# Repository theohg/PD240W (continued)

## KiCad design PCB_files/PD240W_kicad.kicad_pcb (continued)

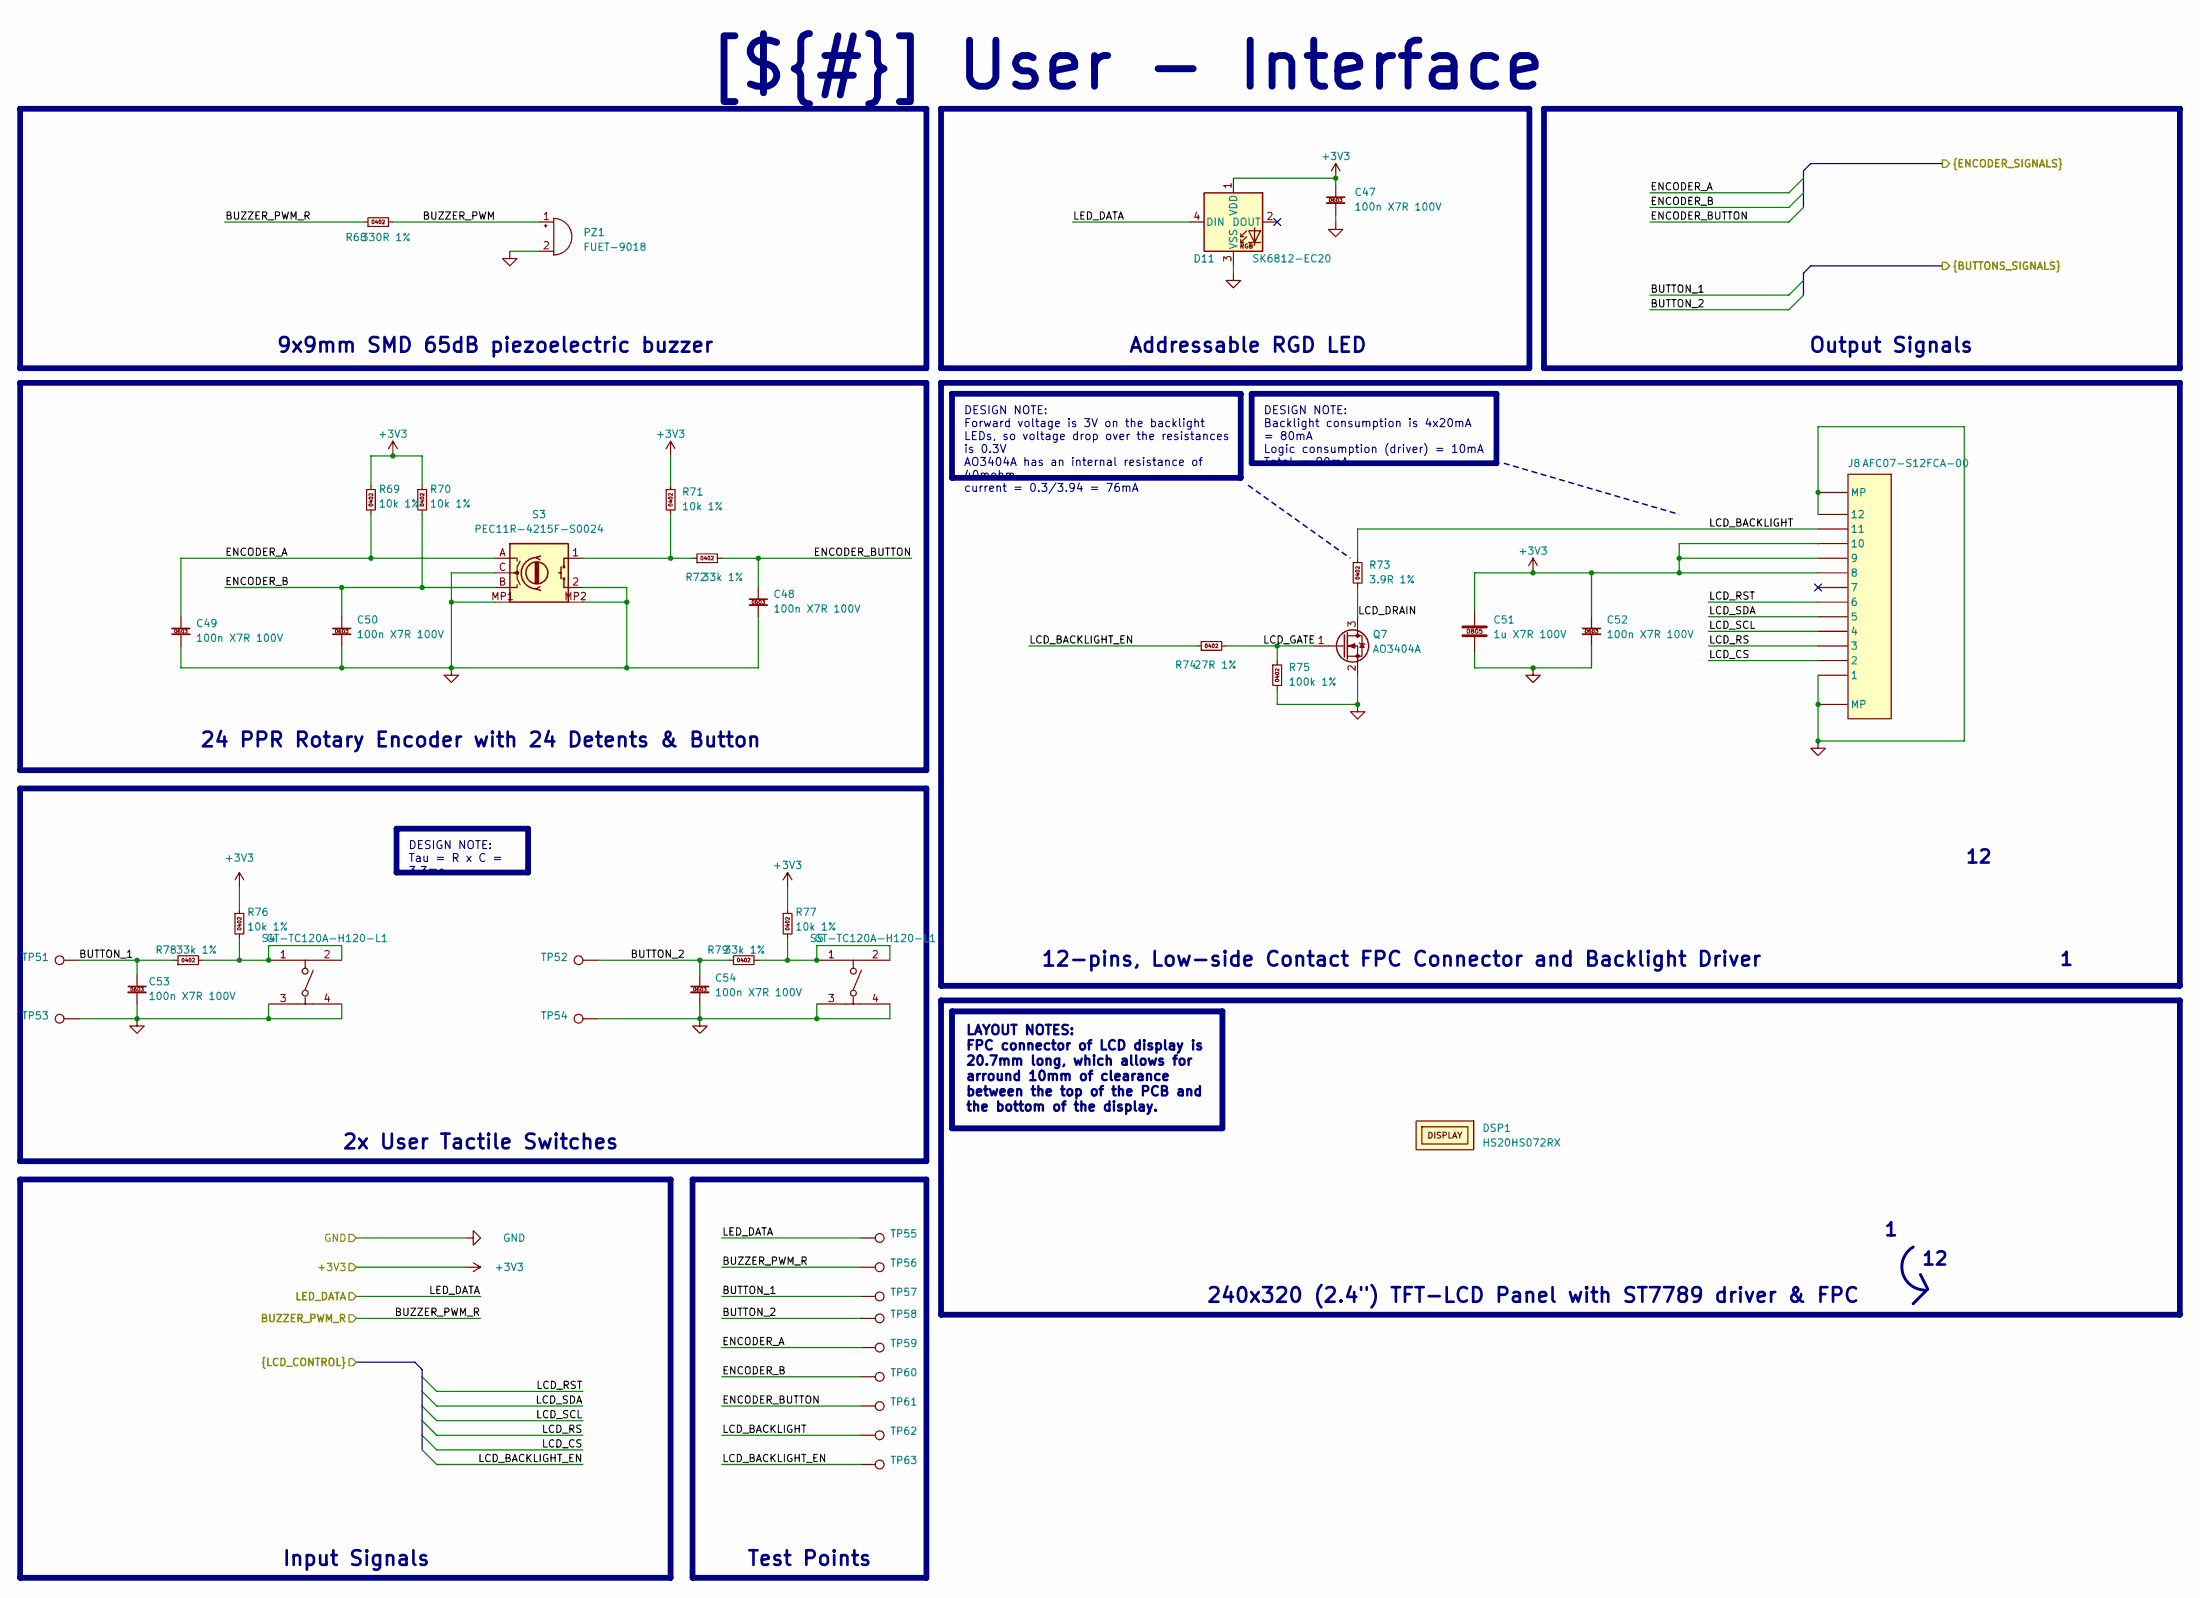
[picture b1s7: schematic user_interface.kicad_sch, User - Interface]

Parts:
C47, C48, C49, C50, C52, C53, C54: 100n X7R 100V; capc_1608_09_l; Manufacturer Part Number CL10B104KC8NNNC; LCSC C15725
C51: 1u X7R 100V; capc_2012_14_n; Manufacturer Part Number CC0805KKX7R0BB105; LCSC C5370002
D11: SK6812-EC20; Manufacturer Part Number SK6812-EC20; LCSC C2909058
DSP1: HS20HS072RX; generic_display_518x362x2_10mm_standoff; Manufacturer Part Number HS20HS072RX; LCSC C5329582
J8: AFC07-S12FCA-00; Manufacturer Part Number AFC07-S12FCA-00; LCSC C262559
PZ1: FUET-9018; buzzer_9x9x2.1mm; Manufacturer Part Number FUET-9018; LCSC C391035
Q7: AO3404A; sot-23-3L_103p_300x130x110_n; Manufacturer Part Number AO3404A; LCSC C30010
R68: 330R 1%; resc_1005_04_m; Manufacturer Part Number 0402WGF3300TCE; LCSC C25104
R69, R70, R71, R76, R77: 10k 1%; resc_1005_04_n; Manufacturer Part Number 0402WGF1002TCE; LCSC C25744
R72, R78, R79: 33k 1%; resc_1005_04_n; Manufacturer Part Number RC0402FR-0733KL; LCSC C138003
R73: 3.9R 1%; resc_1005_04_m; Manufacturer Part Number FRC0402F3R90TS; LCSC C2933095
R74: 27R 1%; resc_1005_04_m; Manufacturer Part Number RC0402FR-0727RL; LCSC C138021
R75: 100k 1%; resc_1005_04_m; Manufacturer Part Number 0402WGF1003TCE; LCSC C25741
S3: PEC11R-4215F-S0024; Manufacturer Part Number PEC11R-4215F-S0024; LCSC C143790
S4, S5: GT-TC120A-H120-L1; Manufacturer Part Number GT-TC120A-H120-L1; LCSC C2762973
TP51, TP52, TP53, TP54: sp_oval_300x100
TP55, TP56, TP57, TP58, TP59, TP60, TP61, TP62, TP63: tp_round_70

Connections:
+3V3: C47.1, C51.1, C52.1, D11.1 (VDD), J8.8, J8.9, J8.10, R69.1, R70.1, R71.1, R76.1, R77.1; also elsewhere on the board
/Project Architecture/MCU - Unit/BUTTON_1: C53.1, R78.1, TP51.1, TP57.1; also elsewhere on the board
/Project Architecture/MCU - Unit/BUTTON_2: C54.1, R79.1, TP52.1, TP58.1; also elsewhere on the board
/Project Architecture/MCU - Unit/BUZZER_PWM_R: R68.1, TP56.1; also elsewhere on the board
/Project Architecture/MCU - Unit/ENCODER_A: C49.1, R69.2, S3.A, TP59.1; also elsewhere on the board
/Project Architecture/MCU - Unit/ENCODER_B: C50.1, R70.2, S3.B, TP60.1; also elsewhere on the board
/Project Architecture/MCU - Unit/ENCODER_BUTTON: C48.1, R72.2, TP61.1; also elsewhere on the board
/Project Architecture/MCU - Unit/LCD_BACKLIGHT_EN: R74.1, TP63.1; also elsewhere on the board
/Project Architecture/MCU - Unit/LCD_CS: J8.2; also elsewhere on the board
/Project Architecture/MCU - Unit/LCD_RS: J8.3; also elsewhere on the board
/Project Architecture/MCU - Unit/LCD_RST: J8.6; also elsewhere on the board
/Project Architecture/MCU - Unit/LCD_SCL: J8.4; also elsewhere on the board
/Project Architecture/MCU - Unit/LCD_SDA: J8.5; also elsewhere on the board
/Project Architecture/MCU - Unit/LED_DATA: D11.4 (DIN), TP55.1; also elsewhere on the board
/Project Architecture/User - Interface/BUZZER_PWM: PZ1.1 (+), R68.2
/Project Architecture/User - Interface/LCD_BACKLIGHT: J8.11, R73.1, TP62.1
/Project Architecture/User - Interface/LCD_DRAIN: Q7.3 (D), R73.2
/Project Architecture/User - Interface/LCD_GATE: Q7.1 (G), R74.2, R75.1
GND: C47.2, C48.2, C49.2, C50.2, C51.2, C52.2, C53.2, C54.2, D11.3 (VSS), J8.1, J8.12, J8.MP1 (MP), J8.MP2 (MP), PZ1.2 (-), Q7.2 (S), R75.2, S3.2, S3.C, S3.MP1, S3.MP2, S4.3, S4.4, S5.3, S5.4, TP53.1, TP54.1; also elsewhere on the board
unnamed: R71.2, R72.1, S3.1
unnamed: R76.2, R78.2, S4.1, S4.2
unnamed: R77.2, R79.2, S5.1, S5.2

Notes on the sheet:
9x9mm SMD 65dB piezoelectric buzzer
Addressable RGD LED
12-pins, Low-side Contact FPC Connector and Backlight Driver
240x320 (2.4") TFT-LCD Panel with ST7789 driver & FPC
24 PPR Rotary Encoder with 24 Detents & Button
Input Signals
Test Points
Output Signals
2x User Tactile Switches
DESIGN NOTE: Backlight consumption is 4x20mA = 80mA Logic consumption (driver) = 10mA Total = 90mA
DESIGN NOTE: Tau = R x C = 3.3ms
DESIGN NOTE: Forward voltage is 3V on the backlight LEDs, so voltage drop over the resistances is 0.3V AO3404A has an internal resistance of 40mohm. current = 0.3/3.94 = 76mA
LAYOUT NOTES: FPC connector of LCD display is 20.7mm long, which allows for arround 10mm of clearance between the top of the PCB and the bottom of the display.
[${#}] ${TITLE}

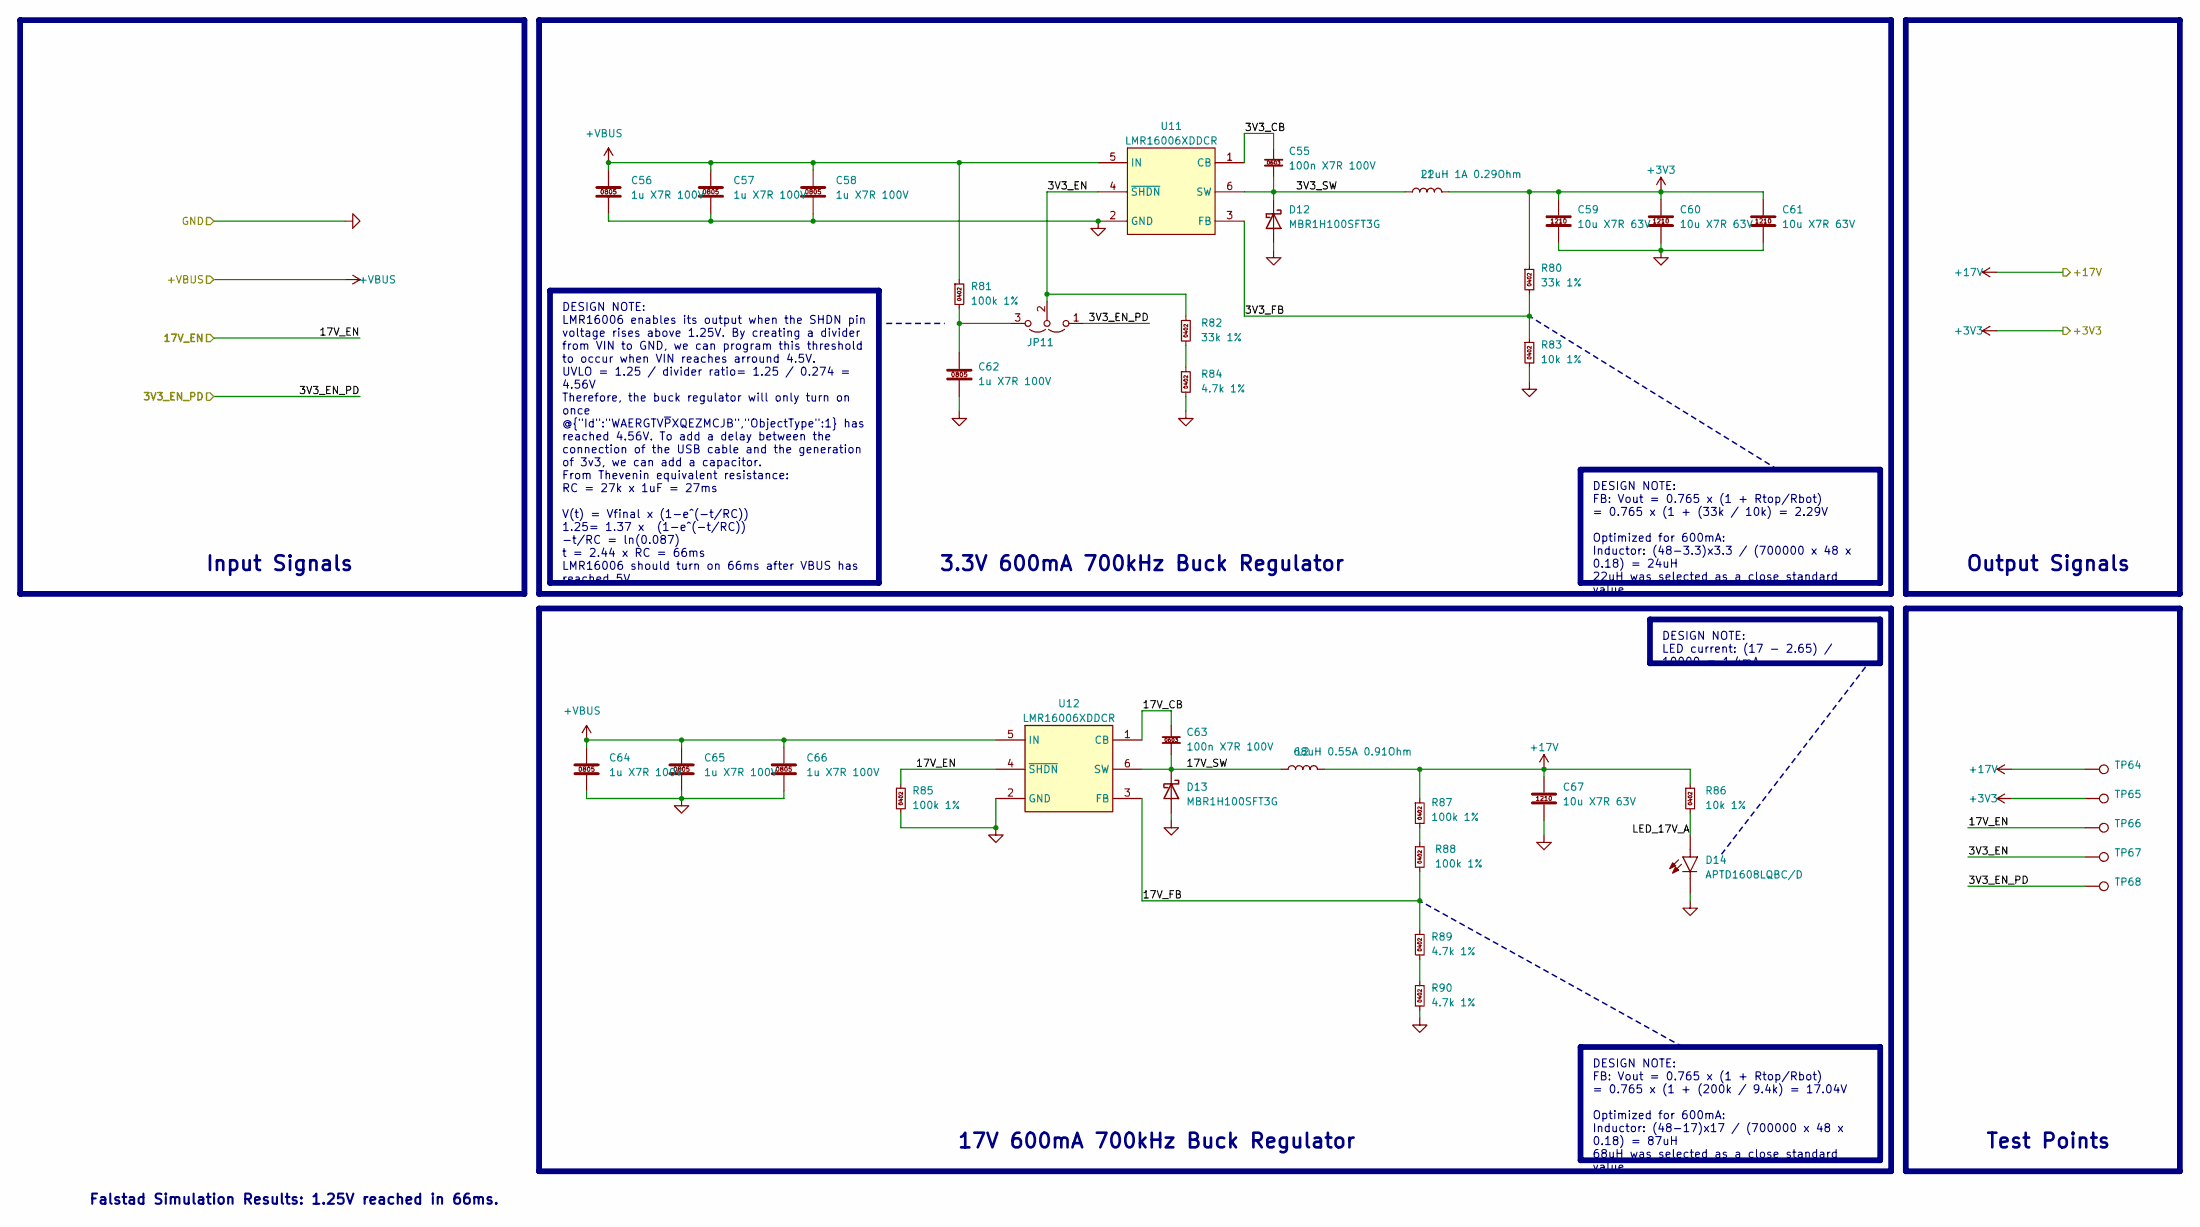
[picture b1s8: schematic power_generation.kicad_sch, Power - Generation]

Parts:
C55, C63: 100n X7R 100V; capc_1608_09_l; Manufacturer Part Number CL10B104KC8NNNC; LCSC C15725
C56, C57, C58, C62, C64, C65, C66: 1u X7R 100V; capc_2012_14_n; Manufacturer Part Number CC0805KKX7R0BB105; LCSC C5370002
C59, C60, C61, C67: 10u X7R 63V; capc_3225_27_n; Manufacturer Part Number GRM32ER71J106KA12L; LCSC C437568
D12, D13: MBR1H100SFT3G; sod-123fl_305p_260x160x90_n; Manufacturer Part Number MBR1H100SFT3G; LCSC C235757
D14: APTD1608LQBC/D; kingbright_0603_blue; Manufacturer Part Number APTD1608LQBC/D; LCSC C5344742
JP11: jumper_solder_3pad_no; jumper_solder_3pad_no_40x40_20
L1: 22uH 1A 0.29Ohm; SWPA4030S220MT; Manufacturer Part Number SWPA4030S220MT; LCSC C83472
L2: 68uH 0.55A 0.91Ohm; SWPA4030S220MT; Manufacturer Part Number ASWPA4035S680MT; LCSC C340217
R80, R82: 33k 1%; resc_1005_04_n; Manufacturer Part Number RC0402FR-0733KL; LCSC C138003
R81, R85, R87, R88: 100k 1%; resc_1005_04_m; Manufacturer Part Number 0402WGF1003TCE; LCSC C25741
R83, R86: 10k 1%; resc_1005_04_n; Manufacturer Part Number 0402WGF1002TCE; LCSC C25744
R84, R89, R90: 4.7k 1%; resc_1005_04_m; Manufacturer Part Number 0402WGF1003TCE; LCSC C25741
TP64, TP65, TP66, TP67, TP68: tp_round_70
U11, U12: LMR16006XDDCR; sot6_p95_290x180x110_n; Manufacturer Part Number LMR16006XDDCR; LCSC C87080

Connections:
+3V3: C59.1, C60.1, C61.1, L1.2, R80.1, TP65.1; also elsewhere on the board
+17V: C67.1, L2.2, R86.1, R87.1, TP64.1; also elsewhere on the board
+VBUS: C56.1, C57.1, C58.1, C64.1, C65.1, C66.1, R81.1, U11.5 (IN), U12.5 (IN); also elsewhere on the board
/Project Architecture/MCU - Unit/17V_EN: R85.1, TP66.1, U12.4 (~SHDN); also elsewhere on the board
/Project Architecture/Power - Generation/3V3_CB: C55.1, U11.1 (CB)
/Project Architecture/Power - Generation/3V3_EN: JP11.2 (C), R82.1, TP67.1, U11.4 (~SHDN)
/Project Architecture/Power - Generation/3V3_EN_PD: JP11.1 (A), TP68.1; also elsewhere on the board
/Project Architecture/Power - Generation/3V3_FB: R80.2, R83.1, U11.3 (FB)
/Project Architecture/Power - Generation/3V3_SW: C55.2, D12.1 (K), L1.1, U11.6 (SW)
/Project Architecture/Power - Generation/17V_CB: C63.1, U12.1 (CB)
/Project Architecture/Power - Generation/17V_FB: R88.2, R89.1, U12.3 (FB)
/Project Architecture/Power - Generation/17V_SW: C63.2, D13.1 (K), L2.1, U12.6 (SW)
/Project Architecture/Power - Generation/LED_17V_A: D14.2 (A), R86.2
GND: C56.2, C57.2, C58.2, C59.2, C60.2, C61.2, C62.2, C64.2, C65.2, C66.2, C67.2, D12.2 (A), D13.2 (A), D14.1 (C), R83.2, R84.2, R85.2, R90.2, U11.2 (GND), U12.2 (GND); also elsewhere on the board
unnamed: C62.1, JP11.3 (B), R81.2
unnamed: R82.2, R84.1
unnamed: R87.2, R88.1
unnamed: R89.2, R90.1

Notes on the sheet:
Input Signals
Output Signals
Test Points
3.3V 600mA 700kHz Buck Regulator
Falstad Simulation Results: 1.25V reached in 66ms.
17V 600mA 700kHz Buck Regulator
DESIGN NOTE: LMR16006 enables its output when the SHDN pin voltage rises above 1.25V. By creating a divider from VIN to GND, we can program this threshold to occur when VIN reaches arround 4.5V. UVLO = 1.25 / divider ratio= 1.25 / 0.274 = 4.56V Therefore, the buck regulator will only turn on once @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
DESIGN NOTE: FB: Vout = 0.765 x (1 + Rtop/Rbot) = 0.765 x (1 + (33k / 10k) = 2.29V Optimized for 600mA: Inductor: (48-3.3)x3.3 / (700000 x 48 x 0.18) = 24uH 22uH was selected as a close standard value.
DESIGN NOTE: LED current: (17 - 2.65) / 10000 = 1.4mA
DESIGN NOTE: FB: Vout = 0.765 x (1 + Rtop/Rbot) = 0.765 x (1 + (200k / 9.4k) = 17.04V Optimized for 600mA: Inductor: (48-17)x17 / (700000 x 48 x 0.18) = 87uH 68uH was selected as a close standard value.

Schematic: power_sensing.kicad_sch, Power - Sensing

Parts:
C23, C24, C25, C26, C27: 100n X7R 100V; capc_1608_09_l; Manufacturer Part Number CL10B104KC8NNNC; LCSC C15725
NT1: nt_2pad_20x20_20_60x20; NetTie-2_SMD_Pad0.5mm
R22: 8m 1%; WSLP1206_n_current_sense_6m_to_50m; Manufacturer Part Number HoLLR1206-1W-8mR-1%; LCSC C2988654
R23, R24, R26: 27R 1%; resc_1005_04_m; Manufacturer Part Number RC0402FR-0727RL; LCSC C138021
R25, R30: 4.7k 1%; resc_1005_04_m; Manufacturer Part Number 0402WGF1003TCE; LCSC C25741
R27, R28, R29: 100k 1%; resc_1005_04_m; Manufacturer Part Number 0402WGF1003TCE; LCSC C25741
R31: 10k 1%; resc_1005_04_n; Manufacturer Part Number 0402WGF1002TCE; LCSC C25744
R32: 10k @25°C; resc_1005_04_m; Manufacturer Part Number SDNT1005X103F3950FTF; LCSC C95939
TP27, TP28, TP29, TP30: tp_round_70
U7: SN74LVC1G17DBVR; sot25_95p_300x280x145_jedec_mo-178-aa_n; Manufacturer Part Number SN74LVC1G17DBVR; LCSC C7836
U8: INA228AIDGSR; vssop10_50p_300x300x110_mfg; Manufacturer Part Number INA228AIDGSR; LCSC C2887910

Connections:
+3V3: C24.1, C25.1, R30.1, U7.5 (VCC), U8.6 (VS); also elsewhere on the board
+VBUS: R27.1, R28.1; also elsewhere on the board
+VBUS_OUT: R22.2, R24.1, TP30.1, U8.8 (VBUS); also elsewhere on the board
+VBUS_SENSED: R22.1, R23.1; also elsewhere on the board
/Project Architecture/MCU - Unit/I2C0_SCL: U8.5 (SCL); also elsewhere on the board
/Project Architecture/MCU - Unit/I2C0_SDA: U8.4 (SDA); also elsewhere on the board
/Project Architecture/MCU - Unit/SW_EN_READ: R25.2, TP29.1; also elsewhere on the board
/Project Architecture/MCU - Unit/TEMP_SENSE: C27.1, R30.2, R32.1; also elsewhere on the board
/Project Architecture/MCU - Unit/V_SENSE: C26.1, R29.2, R31.1, TP27.1; also elsewhere on the board
/Project Architecture/Power - PD Controller/SWITCH_EN: R26.2, TP28.1, U7.2 (A); also elsewhere on the board
/Project Architecture/Power - Sensing/INA_ALERT: R26.1, U8.3 (ALERT)
/Project Architecture/Power - Sensing/SENSE_N: C23.2, R24.2, U8.9 (IN-)
/Project Architecture/Power - Sensing/SENSE_P: C23.1, R23.2, U8.10 (IN+)
GND: C24.2, C25.2, C26.2, C27.2, NT1.2, R31.2, U7.3 (GND), U8.1 (A1), U8.2 (A0), U8.7 (GND); also elsewhere on the board
unnamed: NT1.1, R32.2
unnamed: R27.2, R28.2, R29.1
unnamed: R25.1, U7.4 (Y)

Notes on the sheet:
Test Points
Input Signals
85-V, 20-Bit, Ultra-Precise Power/Energy/Charge Monitor With I²C Interface
Temperature Sensing
Output Signals
Input Voltage Sensing
DESIGN NOTE: B-Constant is 3950K 1.2k @ 80°C -> 0.67V 2.5k @ 60°C -> 1.14V 10k @ 25°C -> 2.24V 13k @ 20°C -> 2.42V
DESIGN NOTE: I2C pullups are on Power - PD Conroller schematic
DEBUG NOTE: INA228AIDGSR address when A1 & A0 are tied to GND is 0x40 (7 bits 1000000) (see page 19)
DESIGN NOTE: ADCRANGE = 1 (+- 40.96 mV range) V_{SENSE} = 5A x 0.008 = 40 mV. This utilizes 97.6% of the ADC range, providing the highest possible resolution. Power Dissipation: P = 5² x 0.008 = 0.2W
LAYOUT NOTES: NTC must be placed close and thermally coupled to the ground plane near the relevant heat source. Route away from noisy traces.
LAYOUT NOTES: Place capacitor close to MCU DC pin. Route away from noisy traces.
[${#}] ${TITLE}
DEBUG NOTE: Low side measurement is used to improve thermal coupling, which invert the maths in software.
DESIGN NOTE: Network ratio = 1/16 = 0.0625 @48V V_SENSE = 3V @5V V_SENSE = 0.31V
DEBUG NOTE: ALERT is open-drain and can be configured to latch or not latch the overcurrent event.
DESIGN NOTE: SN74LVC1G17 is a safety buffer to prevent software mistakes. Driving SWEN_READ cannot activate the power switch.

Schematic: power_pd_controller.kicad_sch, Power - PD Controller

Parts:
C9, C10, C11, C12: 10u X7R 63V; capc_3225_27_n; Manufacturer Part Number GRM32ER71J106KA12L; LCSC C437568
C13, C14, C15: 3.3u X5R 25V; capc_1608_09_n; Manufacturer Part Number TCC0603X5R335M250CT; LCSC C5360803
C16, C17, C21, C22: 100n X7R 100V; capc_1608_09_l; Manufacturer Part Number CL10B104KC8NNNC; LCSC C15725
C18: 2.2u X7R 100V; capc_2012_14_m; Manufacturer Part Number HHV0805R7225K101NSLJ; LCSC C22367838
C19, C20: 220p X7R 50V; capc_1005_06_l; Manufacturer Part Number CL05B221KB5NNNC; LCSC C296710
D5: B0520LW-7-F; sod-123_270x155135_n; Manufacturer Part Number B0520LW-7-F; LCSC C155367
D6: APTD1608LQBC/D; kingbright_0603_blue; Manufacturer Part Number APTD1608LQBC/D; LCSC C5344742
D7: D3V3F4U6S-7; sot363_sc88_65p_200x125x110_n; Manufacturer Part Number D3V3F4U6S-7; LCSC C1869321
J2: 61300411121; we_61300411121; Manufacturer Part Number 61300411121; LCSC C5184785; not fitted
JP3: jumper_solder_3pad_12nc_kicad; SolderJumper-3_P1.3mm_Bridged2Bar12_RoundedPad1.0x1.5mm
JP4, JP5, JP6, JP7, JP8, JP9: jumper_solder_2pad_no; jumper_solder_2pad_no_40x40_20
JP10: jumper_solder_2pad_no_kicad; SolderJumper-2_P1.3mm_Open_RoundedPad1.0x1.5mm
Q3: SQJB90EP-T1_GE3; PowerPAKSO-8_127p_513x615x120_n; Manufacturer Part Number SQJB90EP-T1_GE3; LCSC C727731
Q4, Q5, Q6: AO3404A; sot-23-3L_103p_300x130x110_n; Manufacturer Part Number AO3404A; LCSC C30010
R7: 27R 1%; resc_1005_04_m; Manufacturer Part Number RC0402FR-0727RL; LCSC C138021
R8, R9, R11, R12, R18: 4.7k 1%; resc_1005_04_m; Manufacturer Part Number 0402WGF1003TCE; LCSC C25741
R10, R13, R19: 10k 1%; resc_1005_04_n; Manufacturer Part Number 0402WGF1002TCE; LCSC C25744
R14, R15, R16, R17, R21: 100k 1%; resc_1005_04_m; Manufacturer Part Number 0402WGF1003TCE; LCSC C25741
R20: 330R 1%; resc_1005_04_m; Manufacturer Part Number 0402WGF3300TCE; LCSC C25104
TP14, TP15, TP16, TP17, TP18, TP19, TP20, TP21, TP22, TP23, TP24, TP25, TP26: tp_round_70
U2: LM2765; sot236_p95_290x160x110_n; Manufacturer Part Number LM2765M6X/NOPB; LCSC C140270
U3: TPS26750SRSMR; qfn32_40p_400x400x100_tp_280x280_mfg; Manufacturer Part Number TPS26750SRSMR; LCSC C42166327
U4: LTC7004x; msop_10p_300x490x110_tp168x188_n; Manufacturer Part Number LTC7004EMSE#TRPBF; LCSC C690106
U5: 74LVC1G08SE-7; sot353_65p_200x125x110_mo-203-aa_n; Manufacturer Part Number 74LVC1G08SE-7; LCSC C460522
U6: CAT24C512YI-GT3; JEDEC_MO-153_AA; Manufacturer Part Number CAT24C512YI-GT3; LCSC C56096

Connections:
+1V5_LDO: C9.1, TP22.1, U3.2 (ADCIN1), U3.3 (ADCIN2), U3.4 (LDO_1V5)
+3V3: C11.1, D6.2 (A), D7.5, U3.32 (VIN_3V3); also elsewhere on the board
+3V3_EEPROM: C22.1, J2.1, JP10.1 (A), U6.8 (VCC)
+3V3_LDO: C10.1, C13.1, C21.1, D5.2 (A), JP10.2 (B), R8.1, R9.1, R10.1, R11.1, R12.1, R13.1, R15.1, R16.1, TP24.1, U2.1 (IN), U3.1 (LDO_3V3), U5.5 (VCC); also elsewhere on the board
+6V6_LDO: C14.1, D5.1 (K), TP26.1, U2.5 (OUT), U4.1 (VCC)
+VBUS: JP3.3 (B), Q3.5 (D); also elsewhere on the board
+VBUS_LV: C17.1, U3.26 (VBUS), U3.27 (VBUS); also elsewhere on the board
+VBUS_SENSED: Q3.6 (D), TP20.1; also elsewhere on the board
/Project Architecture/MCU - Unit/GPIO14_R: JP9.2 (B); also elsewhere on the board
/Project Architecture/MCU - Unit/GPIO15_R: JP8.2 (B); also elsewhere on the board
/Project Architecture/MCU - Unit/I2C0_SCL: R9.2, U3.9 (I2CT_SCL); also elsewhere on the board
/Project Architecture/MCU - Unit/I2C0_SDA: R8.2, U3.8 (I2CT_SDA); also elsewhere on the board
/Project Architecture/MCU - Unit/PD_GPIO1: TP15.1, U3.6 (GPIO1); also elsewhere on the board
/Project Architecture/MCU - Unit/PD_GPIO3: TP18.1, U3.18 (GPIO3); also elsewhere on the board
/Project Architecture/MCU - Unit/SWITCH_EN_MANUAL: R21.1, U5.2 (B); also elsewhere on the board
/Project Architecture/MCU - Unit/USB_PD_IRQ: R10.2, TP16.1, U3.10 (*I2CT_IRQ); also elsewhere on the board
/Project Architecture/Power - Generation/3V3_EN_PD: U3.31 (GPIO6); also elsewhere on the board
/Project Architecture/Power - PD Controller/CAP+: C15.1, U2.6 (CAP+)
/Project Architecture/Power - PD Controller/CAP-: C15.2, U2.3 (CAP-)
/Project Architecture/Power - PD Controller/CC1: C20.1, U3.24 (CC1); also elsewhere on the board
/Project Architecture/Power - PD Controller/CC2: C19.1, U3.25 (CC2); also elsewhere on the board
/Project Architecture/Power - PD Controller/EPR_EN: U3.7 (GPIO2); also elsewhere on the board
/Project Architecture/Power - PD Controller/I2CC_IRQ: R13.2, U3.17 (*I2CC_IRQ)
/Project Architecture/Power - PD Controller/I2CC_SCL: JP6.2 (B), U3.16 (I2CC_SCL)
/Project Architecture/Power - PD Controller/I2CC_SCL_EEPROM: JP6.1 (A), JP7.2 (B), JP8.1 (A), R12.2, U6.6 (SCL)
/Project Architecture/Power - PD Controller/I2CC_SCL_EXT: D7.1, J2.2, JP7.1 (A)
/Project Architecture/Power - PD Controller/I2CC_SDA: JP4.2 (B), U3.15 (I2CC_SDA)
/Project Architecture/Power - PD Controller/I2CC_SDA_EEPROM: JP4.1 (A), JP5.2 (B), JP9.1 (A), R11.2, U6.5 (SDA)
/Project Architecture/Power - PD Controller/I2CC_SDA_EXT: D7.6, J2.3, JP5.1 (A)
/Project Architecture/Power - PD Controller/LTC_BST: C18.2, U4.9 (BST)
/Project Architecture/Power - PD Controller/LTC_GATE: Q3.2 (G), Q3.4 (G), R7.2, R14.2, R17.2, TP25.1, U4.6 (TGDN)
/Project Architecture/Power - PD Controller/POWER_PATH_EN: Q4.1 (G), TP14.1, U3.20 (POWER_PATH_EN)
/Project Architecture/Power - PD Controller/PP5V: C12.1, U3.28 (PP5V), U3.29 (PP5V)
/Project Architecture/Power - PD Controller/PP_EN1: Q4.3 (D), Q5.1 (G), R15.2, TP17.1
/Project Architecture/Power - PD Controller/PP_EN2: Q5.3 (D), R16.2, TP19.1, U5.1 (A)
/Project Architecture/Power - PD Controller/PP_EN3: R18.1, R19.1, TP21.1, U5.4 (Y)
/Project Architecture/Power - PD Controller/SWITCH_EN: Q6.1 (G), R18.2, U4.4 (INP); also elsewhere on the board
/Project Architecture/Power - PD Controller/TS: C18.1, JP3.1 (A), JP3.2 (C), Q3.1 (S), Q3.3 (S), TP23.1, U4.8 (TS)
/Project Architecture/Power - PD Controller/~FLT: U3.5 (GPIO0); also elsewhere on the board
GND: C9.2, C10.2, C11.2, C12.2, C13.2, C14.2, C16.2, C17.2, C19.2, C20.2, C21.2, C22.2, D7.2, J2.4, Q4.2 (S), Q5.2 (S), Q6.2 (S), R19.2, R21.2, U2.2 (GND), U2.4 (SD), U3.11 (GND), U3.12 (GND), U3.13 (GPIO11), U3.14 (GND), U3.19 (GND), U3.22 (GPIO4/USB_P/LD1), U3.23 (GPIO5/USB_N/LD2), U3.30 (GPIO7), U3.33 (GND), U4.2 (VCCUV), U4.3 (GND), U4.5 (OVLO), U4.11 (GND), U5.3 (GND), U6.1 (A0), U6.2 (A1), U6.3 (A2), U6.4 (VSS), U6.7 (WP); also elsewhere on the board
unnamed: C16.1, R7.1
unnamed: D6.1 (C), R20.1
unnamed: Q6.3 (D), R20.2
unnamed: R14.1, R17.1, U4.7 (TGUP)

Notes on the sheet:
I²C0
512 Kb I2C CMOS Serial EEPROM
USB Type-C® and USB PD Controller With Integrated Power Switches
Output Signals
Test Points
Input Signals
I²C1
DEBUG NOTE: ADCIN both conected to LDO1.5V result in ADCINx decoded value 5, which activate AlwaysEnableSink mode and I²C address 0x21 (7 bits). (see page 34)
DEBUG NOTE: EEPROM Address: Must be 0x50 (7-bit) on the I2Cc bus for the TPS26750 to find it automatically. (1010000)
DEBUG NOTE: If the gate driver is not working as expected, connect the bootstrap capacitor to +VBUS instead of TS.
LAYOUT NOTE: CC1/CC2 capacitors need to be placed as close as possible to their respective pins and on the same layer as the TPS26750 device.
DESIGN NOTE: 3V3 LDO total current needs to be lower than 5mA at startup: EEPROM read: 1mA POWER OK LED: 0.65mA TPD4S480: 0.16mA LM2765: 0.13mA LTC7004: 0.05mA I²C pull-ups: ~~0.5mA ADC resistors: 0.02mA AND gate: <0.01mA Total ~~2.5mA < 5mA
DESIGN NOTE: The default state for a USB-C port (before or during negotiation, or if negotiation fails) is effectively USB 2.0 specs: 5V @ 500mA. Therefore we want to limit the inrush current. Synapticon drives have an averager of 150uF of input capacitance. As explained in application informations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
DESIGN NOTE: LED current: (3.3 - 2.65)/330 = 2mA
DEBUG NOTE: When flashing the binary configuration to the EEPROM leave the jumper open, and power the EEPROM from an external supply, to avoid I²C bus conflict with TPS26750.
[${#}] ${TITLE}

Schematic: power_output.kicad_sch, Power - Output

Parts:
C28, C29: 10u X7R 63V; capc_3225_27_n; Manufacturer Part Number GRM32ER71J106KA12L; LCSC C437568
C30: 100n X7R 100V; capc_1608_09_l; Manufacturer Part Number CL10B104KC8NNNC; LCSC C15725
D8: SMAJ48A; do-214ac_440p_430x250x230_n_p; Manufacturer Part Number SMAJ48A; LCSC C41376401
F1, F2: FSMD020-1206-R; ptc_1206_08_n; Manufacturer Part Number FSMD020-1206-R; LCSC C220145
J3: 24.245.1; fcr7350r; Manufacturer Part Number 24.245.1; LCSC C7437326
J4: 24.245.2; fcr7350b; Manufacturer Part Number 24.245.2; LCSC C7437327
J5, J6: 1935776; phoenix_1935776; Manufacturer Part Number 1935776; LCSC C3817389
R33, R34: 33k 1%; resc_1005_04_n; Manufacturer Part Number RC0402FR-0733KL; LCSC C138003
TP31, TP32: 5001; Manufacturer Part Number 5001; LCSC C238122; not fitted

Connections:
+3V3: F1.1; also elsewhere on the board
+17V: F2.1; also elsewhere on the board
+VBUS_OUT: C28.1, C29.1, C30.1, D8.1 (A1), J3.1, R33.1, TP31.1; also elsewhere on the board
/Project Architecture/Power - Output/3V3_FUSED: F1.2, J5.1
/Project Architecture/Power - Output/17V_FUSED: F2.2, J6.1, J6.2
GND: C28.2, C29.2, C30.2, D8.2 (A2), J3.MP1 (MP), J3.MP2 (MP), J3.MP3 (MP), J3.MP4 (MP), J4.1, J4.MP1 (MP), J4.MP2 (MP), J4.MP3 (MP), J4.MP4 (MP), J5.2, R34.2, TP32.1; also elsewhere on the board
unnamed: R33.2, R34.1

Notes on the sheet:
Screw Terminals for 17V
4mm Banana SMT RED & BLACK Output Connectors
Input Signals
DESIGN NOTE: V_r : 48V V_brmin : 53.3V V_c = 77.4V This diode is our best option for 48V, but it won't be enough as TPD4S480 has a 63V maximum input voltage, and LMR16006 65V.
DESIGN NOTE: RC = 66k x 20uF = 1.3ms Safe to touch in 3 seconds max power losses: 0.73mA
[${#}] ${TITLE}
DESIGN NOTE: I_hold = 200mA I_trip = 400mA
FCR7350R - C7437326
LAYOUT NOTES: Space Banana connectors by a standard 19.05mm. Add mechanical stitching vias to +VBUS_OUT and GND to provide mechanical anchors against external torque applied to the connectors.
FCR7350B - C7437327

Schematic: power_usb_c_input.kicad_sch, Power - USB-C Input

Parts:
C1, C2, C5: 10n X7R 100V; capc_1005_06_n; Manufacturer Part Number CC0402KRX7R0BB103; LCSC C527014
C3: 4.7u; capc_3225_22_n; Manufacturer Part Number GCM32DC72A475KE02; LCSC C913445
C4, C6, C8: 100n X7R 100V; capc_1608_09_l; Manufacturer Part Number CL10B104KC8NNNC; LCSC C15725
C7: 1u X7R 100V; capc_2012_14_n; Manufacturer Part Number CC0805KKX7R0BB105; LCSC C5370002
D1: SMAJ48A; do-214ac_440p_430x250x230_n_p; Manufacturer Part Number SMAJ48A; LCSC C41376401
D2, D3: BZT52C18SQ; sod-323_230p_170x125x100_n; Manufacturer Part Number BZT52C18SQ; LCSC C2857090
D4: APTD1608LQBC/D; kingbright_0603_blue; Manufacturer Part Number APTD1608LQBC/D; LCSC C5344742
FB1: BLM18SN220TH1D; fer_1608_09_n; Manufacturer Part Number BLM18SN220TH1D; LCSC C710392
J1: DX07S024JJ2R1300; Manufacturer Part Number DX07S024JJ2R1300; LCSC C2977282
JP1: jumper_solder_2pad_nc_kicad; SolderJumper-2_P1.3mm_Bridged2Bar_RoundedPad1.0x1.5mm
JP2: jumper_solder_2pad_no; SolderJumper-2_P1.3mm_Open_RoundedPad1.0x1.5mm
Q1: AGM612AP; vsonp8_65p_330x330x80_mfg; Manufacturer Part Number AGM612AP; LCSC C5349119
Q2: AO3404A; sot-23-3L_103p_300x130x110_n; Manufacturer Part Number AO3404A; LCSC C30010
R1, R3: 100k 1%; resc_1005_04_m; Manufacturer Part Number 0402WGF1003TCE; LCSC C25741
R2, R4: 33k 1%; resc_1005_04_n; Manufacturer Part Number RC0402FR-0733KL; LCSC C138003
R5: 1k 1%; resc_1005_04_m; Manufacturer Part Number 0402WGF1001TCE; LCSC C11702
R6: 10k 1%; resc_1005_04_n; Manufacturer Part Number 0402WGF1002TCE; LCSC C25744
TP1, TP2: sp_oval_300x100
TP3, TP4, TP5, TP6, TP7, TP8, TP9, TP10, TP11, TP12, TP13: tp_round_70
U1: TPD4S480RUKR; wqfn20_40p_300x300x80_tp_170x170_n; Manufacturer Part Number TPD4S480RUKR; LCSC C43131250

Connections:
+3V3_LDO: C7.1, D4.2 (A), R6.1, U1.10 (VPWR); also elsewhere on the board
+VBUS: C4.1, FB1.2, Q1.3 (D), TP8.1, U1.20 (VBUS); also elsewhere on the board
+VBUS_LV: C6.1, D3.1 (K), Q1.1 (S), R1.1, TP9.1, U1.19 (VBUS_LV); also elsewhere on the board
/Project Architecture/MCU - Unit/USB_D_N: U1.14 (SBU2); also elsewhere on the board
/Project Architecture/MCU - Unit/USB_D_P: U1.15 (SBU1); also elsewhere on the board
/Project Architecture/Power - PD Controller/CC1: TP3.1, U1.12 (CC1); also elsewhere on the board
/Project Architecture/Power - PD Controller/CC2: TP5.1, U1.11 (CC2); also elsewhere on the board
/Project Architecture/Power - PD Controller/EPR_EN: TP11.1, U1.16 (EPR_EN); also elsewhere on the board
/Project Architecture/Power - PD Controller/~FLT: R6.2, TP12.1, U1.9 (~FLT); also elsewhere on the board
/Project Architecture/Power - USB-C Input/+VBUS_C: C1.1, C2.1, C3.1, D1.1 (A1), FB1.1, J1.A4, J1.A9, J1.B4, J1.B9, TP1.1, TP7.1
/Project Architecture/Power - USB-C Input/+VBUS_LV/2: Q2.1 (G), R1.2, R3.1, TP13.1
/Project Architecture/Power - USB-C Input/CC1_C: J1.A5, TP4.1, U1.4 (C_CC1), U1.7 (RPD_G1)
/Project Architecture/Power - USB-C Input/CC2_C: J1.B5, TP6.1, U1.5 (C_CC2), U1.6 (RPD_G2)
/Project Architecture/Power - USB-C Input/EPR_BLK_G: C5.2, JP2.1 (A), R2.2, TP10.1, U1.17 (EPR_BLK_G)
/Project Architecture/Power - USB-C Input/LED_IN_D: Q2.3 (D), R5.2
/Project Architecture/Power - USB-C Input/LED_IN_K: D4.1 (C), R5.1
/Project Architecture/Power - USB-C Input/USB_D_C_N: J1.A7, J1.B7, U1.2 (C_SBU2)
/Project Architecture/Power - USB-C Input/USB_D_C_P: J1.A6, J1.B6, U1.1 (C_SBU1)
/Project Architecture/Power - USB-C Input/VBIAS: C8.1, U1.3 (VBIAS)
/Project Architecture/Power - USB-C Input/VBUS_LV_GATE: C5.1, D2.1 (K), JP1.1 (A), JP1.2 (B), JP2.2 (B), Q1.2 (G), R2.1
GND: C1.2, C2.2, C3.2, C4.2, C6.2, C7.2, C8.2, D1.2 (A2), J1.A1, J1.A12, J1.B1, J1.B12, J1.MP1 (MP), J1.MP2 (MP), J1.MP3 (MP), J1.MP4 (MP), Q2.2 (S), R4.2, TP2.1, U1.8 (GND), U1.13 (GND), U1.18 (GND), U1.21 (EP); also elsewhere on the board
unnamed: D2.2 (A), D3.2 (A)
unnamed: R3.2, R4.1

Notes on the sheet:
USB Type-C™ 48V EPR port protector with short-to-VBUS overvoltage and IEC ESD protection
Test Points
Output Signals
Input Signals
USB-C 3.2 Gen2 48V 5A SMD receptacle
DEBUG NOTE: FLT is open-drain and requires a pull-up. To save board space, it could be removed, as TPS26750 has configurable internal pull-ups.
DESIGN NOTE: TPD4S480 have only 4uA of sourcing curent at EPR_BLK_G. BZT52C18SQ have a maximum leakage current of 0.1uA. Worst case sinking current: (21.17V - 17.1) / 33000 = 123 uA Turn-on time = 10nF x 12V / 4uA = 12ms
LAYOUT NOTE: Place the capacitors next to the VBUS pins.
DESIGN NOTE: 22ohm @ 100Mhz 4mohm @ DC 8A rated @ 85°C
[${#}] ${TITLE}
DESIGN NOTE: (3.3 - 2.65)/1000 = 0.65mA During dead-battery boot mode, TPS26750 internal LDO's can only source 5mA, this is why LED current as been reduced.
DESIGN NOTE: V_r : 48V V_brmin : 53.3V V_c = 77.4V This diode is our best option for 48V, but it won't be enough as TPD4S480 has a 63V maximum input voltage, and LMR16006 65V.
DEBUG NOTE: +VBUS_C and GND solder pads to test PCB with external supply at limited current.
DESIGN NOTE: +VBUS_LV/2 = 2.85V @ +VBUS_LV = 5V (min) 14.3V @ +VBUS_LV/2 = 25V (max) Vgs th < +VBUS_LV/2 < Vgs max 2.6V < +VBUS_LV/2 < 20V
DESIGN NOTE: VBUS blocking fet needs to have Vds ≥ 48V (in case TPD fails) and Vgs ≥ 0.42 x 50.4V = 21.16V. Since most FETs in this package have a +- 20V Vgs, zener diodes are used to clamp Vgs to 18V.
DESIGN NOTE: Pin A6 & B6 as well as A7 & B7 need to be connected together, to be able to use he USB-C connector in both directions.
DESIGN NOTE: RPD_G1/2 need to be tied to C_CC1/2 to enable dead battery support, to allow the device to be detected as a source by the USB-C source.
